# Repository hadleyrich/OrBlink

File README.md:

OrBlink
=======
Copyright 2013 nice technology Ltd  
Website: <http://nicegear.co/orblink>

An open source USB controlled RGB LED designed to go inside a small
plastic orb. Allows you to control the LED to any color meaning
you can indicate whatever you can imagine from a computer or other
USB host device.

Features:

 * Acts as a human interface device (HID) meaning it doesn't
   need drivers on Linux, Mac or Windows.
 * Based on the Atmel ATTiny85 like many other similar projects so
   you can use the firmware of your choice.
 * Supplied with example code for multiple operating systems.

LICENSE
-------
The hardware design files are licensed under the TAPR Open Hardware License
(www.tapr.org/OHL). See the "hardware/LICENSE" file within this repository
for the full license in plain text format.

The software is licensed under various open source licenses, please see the
LICENSE file within each directory or header in the source code files.

INSTALLATION
------------
The design is saved as an EAGLE project. EAGLE PCB design software is
available from www.cadsoftusa.com free for non-commercial use. To use
this project download it and place the directory containing these files
into the "eagle" directory on your computer. Then open EAGLE and
navigate to Projects -> eagle -> OrBlink.

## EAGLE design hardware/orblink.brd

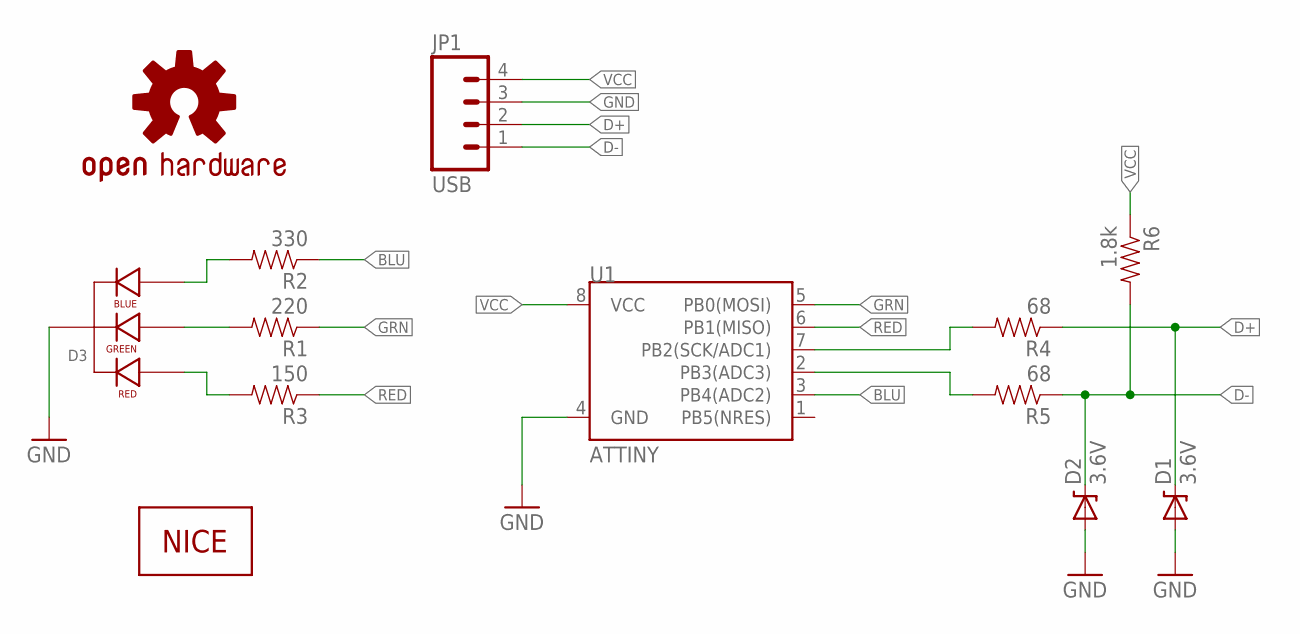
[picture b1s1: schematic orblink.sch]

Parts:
D1, D2: 3.6V; DIODE-ZENER
D3: LED-RGB-CC-THRUDIFFUSE; LED-RGB-THRU
JP1: USB; 1X04
LOGO1: OSHW-LOGOS; OSHW-LOGO-S
R1: 220; 1/6W-RES
R2: 330; 1/6W-RES
R3: 150; 1/6W-RES
R4, R5: 68; 1/6W-RES
R6: 1.8k; 1/6W-RES
U1: ATTINY; DIP08
U$1: NICE-LOGO04; NICE-LOGO-04

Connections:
BLU: R2.1, U1.3 (PB4(ADC2))
D+: D1.P$1 (C), JP1.2, R4.1
D-: D2.P$1 (C), JP1.1, R5.1, R6.2
GND: D1.P$2 (A), D2.P$2 (A), D3.2 (CATHODE), JP1.3, U1.4 (GND)
GRN: R1.1, U1.5 (PB0(MOSI))
unnamed: D3.4 (BLUE_CATHODE), R2.2
unnamed: D3.3 (GREEN_CATHODE), R1.2
unnamed: R4.2, U1.7 (PB2(SCK/ADC1))
unnamed: R5.2, U1.2 (PB3(ADC3))
unnamed: D3.1 (RED_CATHODE), R3.2
RED: R3.1, U1.6 (PB1(MISO))
VCC: JP1.4, R6.1, U1.8 (VCC)

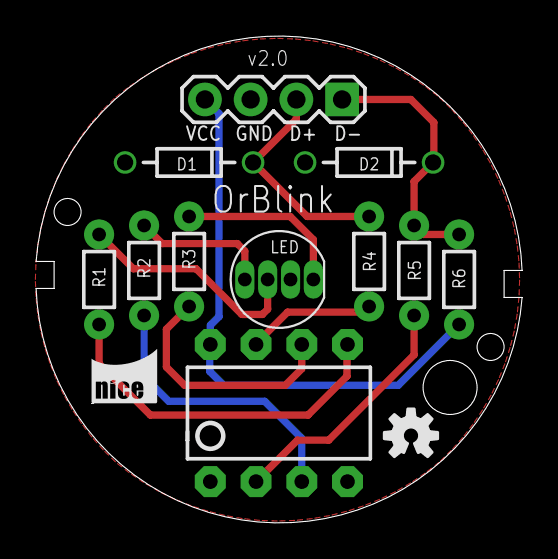
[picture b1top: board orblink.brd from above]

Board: 2 copper layers, 27.0 x 27.0 mm, 13 parts (0 on the bottom side), 12 nets.

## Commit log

2013-05-19 Switched LED and USB pin
2013-05-31 Add Python example code
2013-06-20 Move hardware design files and python code to subdirectories
2013-06-20 Add firmware and C commandline code
2013-06-26 Clarify licensing for individual parts.
2014-01-13 update 'pyusb module is needed' message to make it clear that a version newer than 0.x is needed
2014-01-13 expand commandline not found message to also mention that device not found can be casued be lack of permissions as well
2014-01-13 add sample udev rules file for making the device file accessiable to non root users under Linux
2015-04-07 Add hack to help running Python libusb on OpenELEC
2015-04-07 Add initial functionality to store current values in EEPROM
2015-04-07 Remove dodgy quotes that snuck in somehow
2015-04-07 Require pyusb==1.0.0b2 due to API change
2015-04-07 Add ignores
2015-04-09 Split into module and script
2015-04-09 Ignore compiled python
2015-04-09 Use argparse
2015-04-09 Add hex to rgb function. Add initial delay handling.
2015-04-09 Ignore venv helper file
2015-04-10 Fix quotes

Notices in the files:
parts and their libraries:
SparkFun-DigitalIC: Licensing: CC v3.0 Share-Alike You are welcome to use this library for commercial purposes.
